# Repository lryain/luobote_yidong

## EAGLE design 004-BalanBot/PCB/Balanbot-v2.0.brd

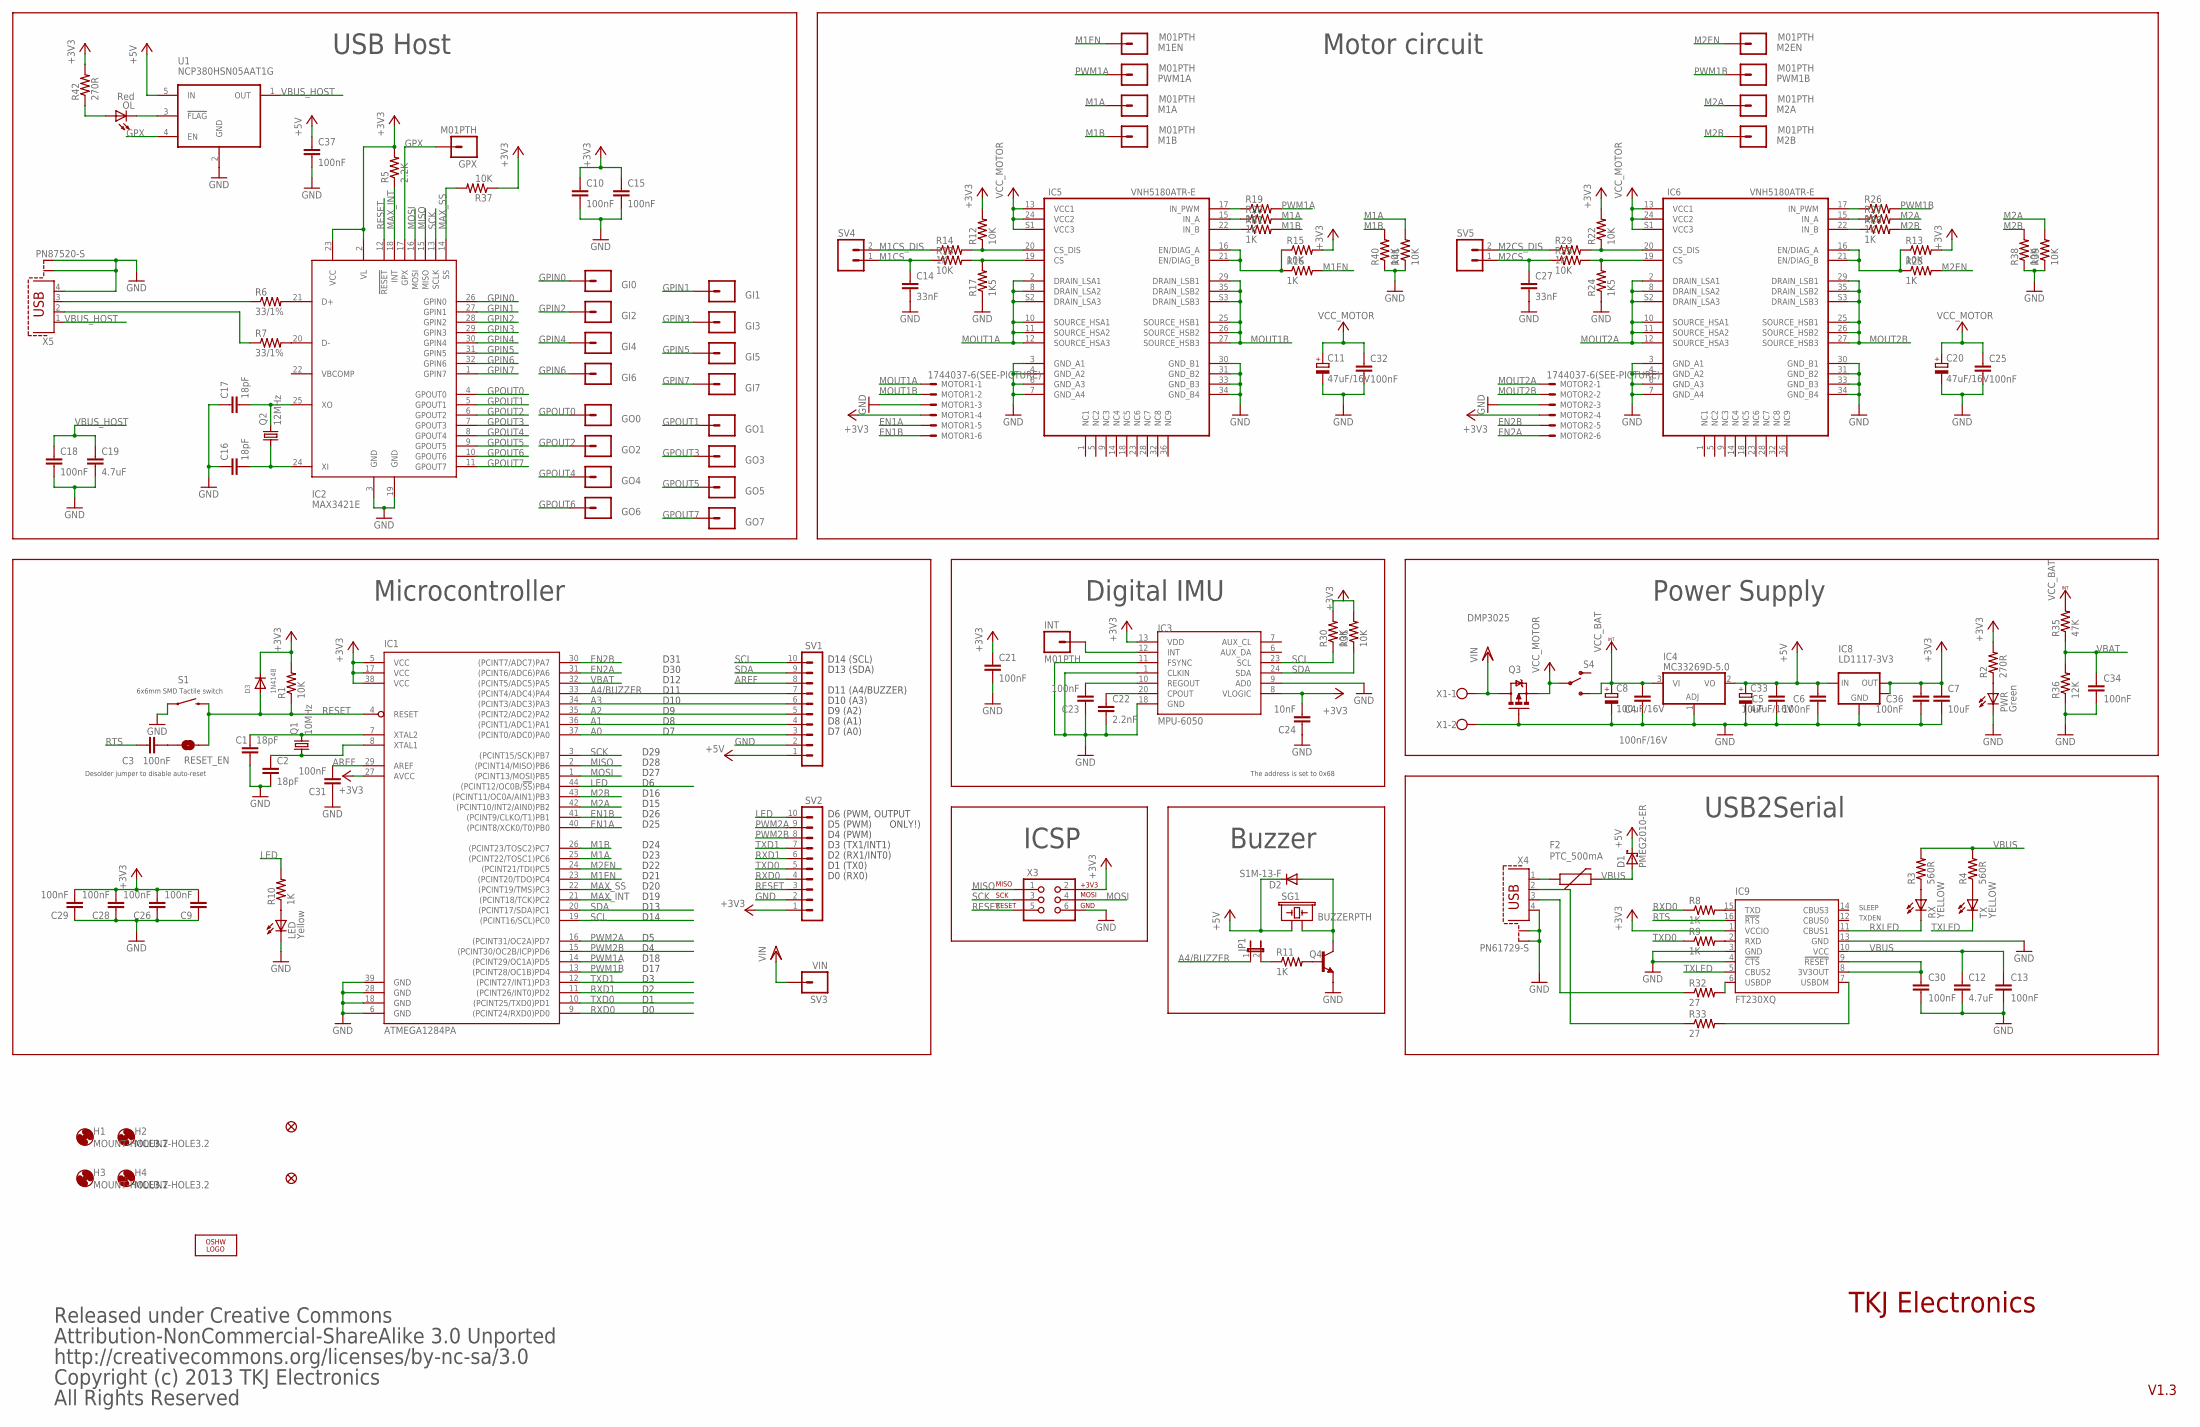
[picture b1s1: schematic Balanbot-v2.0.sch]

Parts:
C1, C2, C16, C17: 18pF; C0603
C3, C6, C9, C10, C13, C15, C18, C21, C23, C25, C26, C28, C29, C30, C31, C32, C34, C36, C37: 100nF; C0603
C4: 100nF/16V; C0603
C5, C7: 10uF; C0805
C8: 100uF/16V; PANASONIC_D
C11, C20, C33: 47uF/16V; PANASONIC_C
C12, C19: 4.7uF; C0805
C14, C27: 33nF; C0603
C22: 2.2nF; C0603
C24: 10nF; C0603
D1: PMEG2010-ER; SOD123
D2: S1M-13-F; DO214AC
D3: 1N4148; SOD-523
F2: PTC_500mA; PTC-1206
GI0, GI1, GI2, GI3, GI4, GI5, GI6, GI7: M01PTH; 1X01
GO0, GO1, GO2, GO3, GO4, GO5, GO6, GO7: M01PTH; 1X01
GPX: M01PTH; 1X01
H1, H2, H3, H4: MOUNT-HOLE3.2; 3,2
IC1: ATMEGA1284PA; TQFP44
IC2: MAX3421E; TQFP32_8MIL
IC3: MPU-6050; TESTING_QFN-24-4MM2
IC4: MC33269D-5.0; DPACK
IC5, IC6: VNH5180ATR-E; POWERSSO-36
IC8: LD1117-3V3; SOT223
IC9: FT230XQ; QFN16
INT: M01PTH; 1X01
JP1: JP1E; JP1
JP2: FIDUCIALUFIDUCIAL; MICRO-FIDUCIAL
JP3: FIDUCIAL1X2; FIDUCIAL-1X2
LED: Yellow; CHIPLED_0805
LOGO2: OSHW_LOGO_FILLX0200-NT; OSHW_FILLX200_NOTEXT
M1A, M1B, M1EN, M2A, M2B, M2EN: M01PTH; 1X01
MOTOR1, MOTOR2: 1744037-6(SEE-PICTURE); 22-23-2061
OL: Red; CHIPLED_0805
PWM1A, PWM1B: M01PTH; 1X01
PWR: Green; CHIPLED_0805
Q1: 10MHz; HC49UP
Q2: 12MHz; HC49UP
Q3: DMP3025; DPAK
Q4: TRANSISTOR_NPNSOT23-3; SOT23-3
R1, R12, R13, R15, R18, R22, R25, R30, R31, R37, R38, R39, R40, R41: 10K; R0603
R2, R42: 270R; R0603
R3, R4: 560R; R0603
R5: 2.2K; R0603
R6, R7: 33/1%; R0603
R8, R9, R10, R11, R14, R16, R19, R20, R21, R23, R26, R27, R28, R29: 1K; R0603
R17, R24: 1K5; R0603
R32, R33: 27; R0603
R35: 47K; R0603
R36: 12K; R0603
RESET_EN: SOLDERJUMPERNC; SJ_2S
RX: YELLOW; CHIPLED_0805
S1: DTSM-62K-S-V-T/R(SN431); TACTILE_SWITCH_TALL
S4: SWITCH-SPDTML; SWITCH-SPDT
SG1: BUZZERPTH; BUZZER-12MM
SV1, SV2: MA10-1
SV3: VIN; 1X01
SV4, SV5: M02PTH; 1X02
TX: YELLOW; CHIPLED_0805
U1: NCP380HSN05AAT1G; SOT23-5
X1: W237-102
X3: AVR_SPI_PRG_62X3_LOCK; 2X3_LOCK
X4: PN61729-S
X5: PN87520-S

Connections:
+3V3: C7.1, C9.2, C10.1, C15.1, C21.1, C24.2, C26.2, C28.2, C29.2, C36.2, D3.K (C), IC1.5 (VCC), IC1.17 (VCC), IC1.27 (AVCC), IC1.38 (VCC), IC2.2 (VL), IC2.23 (VCC), IC3.8 (VLOGIC), IC3.13 (VDD), IC8.2 (OUT), IC8.4 (OUT), IC9.1 (VCCIO), MOTOR1.4, MOTOR2.4, R1.2, R2.2, R5.2, R12.2, R13.2, R15.2, R22.2, R30.2, R31.2, R37.1, R42.2, SV2.1, X3.2
+5V: C5.1, C6.2, C33.+, C37.1, D1.C, D2.C, IC4.2 (VO), IC8.3 (IN), SG1.+ (1), SV1.1, U1.5 (IN)
A0: IC1.37 ((PCINT0/ADC0)PA0), SV1.3
A1: IC1.36 ((PCINT1/ADC1)PA1), SV1.4
A2: IC1.35 ((PCINT2/ADC2)PA2), SV1.5
A3: IC1.34 ((PCINT3/ADC3)PA3), SV1.6
A4/BUZZER: IC1.33 ((PCINT4/ADC4)PA4), JP1.1, SV1.7
AREF: C31.2, IC1.29 (AREF), SV1.8
EN1A: IC1.40 ((PCINT8/XCK0/T0)PB0), MOTOR1.5
EN1B: IC1.41 ((PCINT9/CLKO/T1)PB1), MOTOR1.6
EN2A: IC1.31 ((PCINT6/ADC6)PA6), MOTOR2.6
EN2B: IC1.30 ((PCINT7/ADC7)PA7), MOTOR2.5
GND: C1.1, C2.2, C4.1, C5.2, C6.1, C7.2, C8.-, C9.1, C10.2, C11.-, C12.2, C13.1, C14.2, C15.2, C16.1, C17.1, C18.2, C19.2, C20.-, C21.2, C22.2, C23.1, C24.1, C25.2, C26.1, C27.2, C28.1, C29.1, C30.1, C31.1, C32.2, C33.-, C34.1, C36.1, C37.2, IC1.6 (GND), IC1.18 (GND), IC1.28 (GND), IC1.39 (GND), IC2.3 (GND), IC2.19 (GND), IC3.1 (CLKIN), IC3.9 (AD0), IC3.11 (FSYNC), IC3.18 (GND), IC4.1 (ADJ), IC5.3 (GND_A1), IC5.4 (GND_A2), IC5.6 (GND_A3), IC5.7 (GND_A4), IC5.30 (GND_B1), IC5.31 (GND_B2), IC5.33 (GND_B3), IC5.34 (GND_B4), IC6.3 (GND_A1), IC6.4 (GND_A2), IC6.6 (GND_A3), IC6.7 (GND_A4), IC6.30 (GND_B1), IC6.31 (GND_B2), IC6.33 (GND_B3), IC6.34 (GND_B4), IC8.1 (GND), IC9.3 (GND), IC9.4 (!CTS), IC9.13 (GND), LED.C, MOTOR1.3, MOTOR2.3, PWR.C, Q3.1 (G), Q4.2 (E), R17.1, R24.1, R36.1, R38.1, R39.1, R40.1, R41.1, S1.A2 (1), SV1.2, SV2.2, U1.2 (GND), X1.2, X3.6, X4.4, X4.S1, X4.S2, X5.4, X5.S1, X5.S2
GPIN0: GI0.1, IC2.26 (GPIN0)
GPIN1: GI1.1, IC2.27 (GPIN1)
GPIN2: GI2.1, IC2.28 (GPIN2)
GPIN3: GI3.1, IC2.29 (GPIN3)
GPIN4: GI4.1, IC2.30 (GPIN4)
GPIN5: GI5.1, IC2.31 (GPIN5)
GPIN6: GI6.1, IC2.32 (GPIN6)
GPIN7: GI7.1, IC2.1 (GPIN7)
GPOUT0: GO0.1, IC2.4 (GPOUT0)
GPOUT1: GO1.1, IC2.5 (GPOUT1)
GPOUT2: GO2.1, IC2.6 (GPOUT2)
GPOUT3: GO3.1, IC2.7 (GPOUT3)
GPOUT4: GO4.1, IC2.8 (GPOUT4)
GPOUT5: GO5.1, IC2.9 (GPOUT5)
GPOUT6: GO6.1, IC2.10 (GPOUT6)
GPOUT7: GO7.1, IC2.11 (GPOUT7)
GPX: GPX.1, IC2.17 (GPX), U1.4 (EN)
LED: IC1.44 ((PCINT12/OC0B/!SS!)PB4), R10.2, SV2.10
M1A: IC1.25 ((PCINT22/TOSC1)PC6), M1A.1, R20.2, R41.2
M1B: IC1.26 ((PCINT23/TOSC2)PC7), M1B.1, R21.2, R40.2
M1CS: C14.1, R18.1, SV4.1
M1CS_DIS: R14.1, SV4.2
M1EN: IC1.23 ((PCINT20/TDO)PC4), M1EN.1, R16.2
M2A: IC1.42 ((PCINT10/INT2/AIN0)PB2), M2A.1, R27.2, R39.2
M2B: IC1.43 ((PCINT11/OC0A/AIN1)PB3), M2B.1, R28.2, R38.2
M2CS: C27.1, R25.1, SV5.1
M2CS_DIS: R29.1, SV5.2
M2EN: IC1.24 ((PCINT21/TDI)PC5), M2EN.1, R23.2
MAX_INT: IC1.21 ((PCINT18/TCK)PC2), IC2.18 (INT), R5.1
MAX_SS: IC1.22 ((PCINT19/TMS)PC3), IC2.14 (SS), R37.2
MISO: IC1.2 ((PCINT14/MISO)PB6), IC2.15 (MISO), X3.1
MOSI: IC1.1 ((PCINT13/MOSI)PB5), IC2.16 (MOSI), X3.4
MOUT1A: IC5.2 (DRAIN_LSA1), IC5.8 (DRAIN_LSA2), IC5.10 (SOURCE_HSA1), IC5.11 (SOURCE_HSA2), IC5.12 (SOURCE_HSA3), IC5.S2 (DRAIN_LSA3), MOTOR1.1
MOUT1B: IC5.25 (SOURCE_HSB1), IC5.26 (SOURCE_HSB2), IC5.27 (SOURCE_HSB3), IC5.29 (DRAIN_LSB1), IC5.35 (DRAIN_LSB2), IC5.S3 (DRAIN_LSB3), MOTOR1.2
MOUT2A: IC6.2 (DRAIN_LSA1), IC6.8 (DRAIN_LSA2), IC6.10 (SOURCE_HSA1), IC6.11 (SOURCE_HSA2), IC6.12 (SOURCE_HSA3), IC6.S2 (DRAIN_LSA3), MOTOR2.1
MOUT2B: IC6.25 (SOURCE_HSB1), IC6.26 (SOURCE_HSB2), IC6.27 (SOURCE_HSB3), IC6.29 (DRAIN_LSB1), IC6.35 (DRAIN_LSB2), IC6.S3 (DRAIN_LSB3), MOTOR2.2
unnamed: C3.2, RESET_EN.1
unnamed: C2.1, IC1.8 (XTAL1), Q1.1
unnamed: C1.2, IC1.7 (XTAL2), Q1.2
unnamed: D2.A, Q4.3 (C), SG1.- (2)
unnamed: JP1.2, R11.1
unnamed: R33.1, X4.2
unnamed: LED.A, R10.1
unnamed: OL.A, R42.1
unnamed: PWR.A, R2.1
unnamed: R32.1, X4.3
unnamed: IC9.7 (USBDM), R33.2
unnamed: OL.C, U1.3 (!FLAG)
unnamed: IC2.20 (D-), R7.2
unnamed: IC2.21 (D+), R6.2
unnamed: R6.1, X5.3
unnamed: R7.1, X5.2
unnamed: C17.2, IC2.25 (XO), Q2.2
unnamed: C16.2, IC2.24 (XI), Q2.1
unnamed: IC3.12 (INT), INT.1
unnamed: C22.1, IC3.20 (CPOUT)
unnamed: C23.2, IC3.10 (REGOUT)
unnamed: IC6.16 (EN/DIAG_A), IC6.21 (EN/DIAG_B), R13.1, R23.1
unnamed: IC6.19 (CS), R24.2, R25.2
unnamed: IC5.16 (EN/DIAG_A), IC5.21 (EN/DIAG_B), R15.1, R16.1
unnamed: Q4.1 (B), R11.2
unnamed: IC5.19 (CS), R17.2, R18.2
unnamed: IC5.20 (CS_DIS), R12.1, R14.2
unnamed: IC5.22 (IN_B), R21.1
unnamed: IC5.15 (IN_A), R20.1
unnamed: IC5.17 (IN_PWM), R19.1
unnamed: IC6.22 (IN_B), R28.1
unnamed: IC6.15 (IN_A), R27.1
unnamed: IC6.17 (IN_PWM), R26.1
unnamed: IC6.20 (CS_DIS), R22.1, R29.2
unnamed: F2.1, X4.1
unnamed: IC9.15 (TXD), R8.2
unnamed: IC9.2 (RXD), R9.2
unnamed: IC9.6 (USBDP), R32.2
unnamed: C30.2, IC9.8 (3V3OUT), IC9.9 (!RESET)
unnamed: R3.1, RX.A
unnamed: R4.1, TX.A
PWM1A: IC1.14 ((PCINT29/OC1A)PD5), PWM1A.1, R19.2
PWM1B: IC1.13 ((PCINT28/OC1B)PD4), PWM1B.1, R26.2
PWM2A: IC1.16 ((PCINT31/OC2A)PD7), SV2.9
PWM2B: IC1.15 ((PCINT30/OC2B/ICP)PD6), SV2.8
RESET: D3.A, IC1.4 (RESET), IC2.12 (!RESET), R1.1, RESET_EN.2, S1.B2 (2), SV2.3, X3.5
RTS: C3.1, IC9.16 (!RTS)
RXD0: IC1.9 ((PCINT24/RXD0)PD0), R8.1, SV2.4
RXD1: IC1.11 ((PCINT26/INT0)PD2), SV2.6
RXLED: IC9.11 (CBUS1), RX.C
SCK: IC1.3 ((PCINT15/SCK)PB7), IC2.13 (SCLK), X3.3
SCL: IC1.19 ((PCINT16/SCL)PC0), IC3.23 (SCL), R30.1, SV1.10
SDA: IC1.20 ((PCINT17/SDA)PC1), IC3.24 (SDA), R31.1, SV1.9
TXD0: IC1.10 ((PCINT25/TXD0)PD1), R9.1, SV2.5
TXD1: IC1.12 ((PCINT27/INT1)PD3), SV2.7
TXLED: IC9.5 (CBUS2), TX.C
VBAT: C34.2, IC1.32 ((PCINT5/ADC5)PA5), R35.1, R36.2
VBUS: C12.1, C13.2, D1.A, F2.2, IC9.10 (VCC), R3.2, R4.2
VBUS_HOST: C18.1, C19.1, U1.1 (OUT), X5.1
VCC: C11.+, C20.+, C25.1, C32.1, IC5.13 (VCC1), IC5.24 (VCC2), IC5.S1 (VCC3), IC6.13 (VCC1), IC6.24 (VCC2), IC6.S1 (VCC3), Q3.3 (S), S4.2
VCC_INT: C4.2, C8.+, IC4.3 (VI), R35.2, S4.1 (S)
VDD: Q3.4 (D), SV3.1, X1.1

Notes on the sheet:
Desolder jumper to disable auto-reset
ICSP
Power Supply
D10
D11
D12
D30
D31
D14
D13
D19
D20
D21
D22
D23
D24
D25
D26
D15
D17
D18
D16
D27
D28
D29
D0 (RX0)
D1 (TX0)
D2 (RX1/INT0)
D13 (SDA)
D14 (SCL)
D5 (PWM)
D6 (PWM, OUTPUT
D4 (PWM)
D3 (TX1/INT1)
D10 (A3)
D9 (A2)
D8 (A1)
D7 (A0)
USB2Serial
Digital IMU

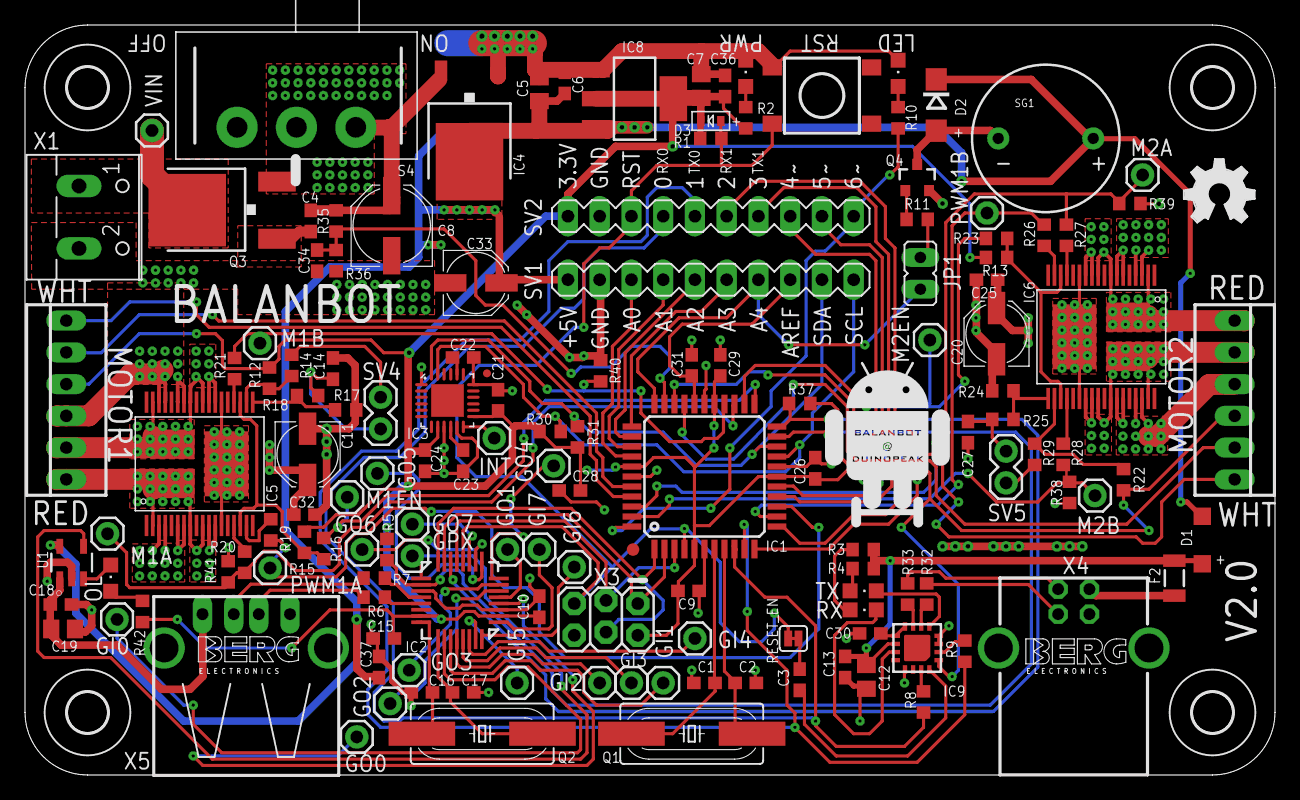
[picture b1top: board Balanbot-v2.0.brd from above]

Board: 2 copper layers, 100.0 x 60.0 mm, 150 parts (1 on the bottom side), 111 nets.

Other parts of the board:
U$2: DUINOPEAK-ANDROID-LOGO-0.65
U$3: DUINOPEAK-ANDROID-LOGO-3.5

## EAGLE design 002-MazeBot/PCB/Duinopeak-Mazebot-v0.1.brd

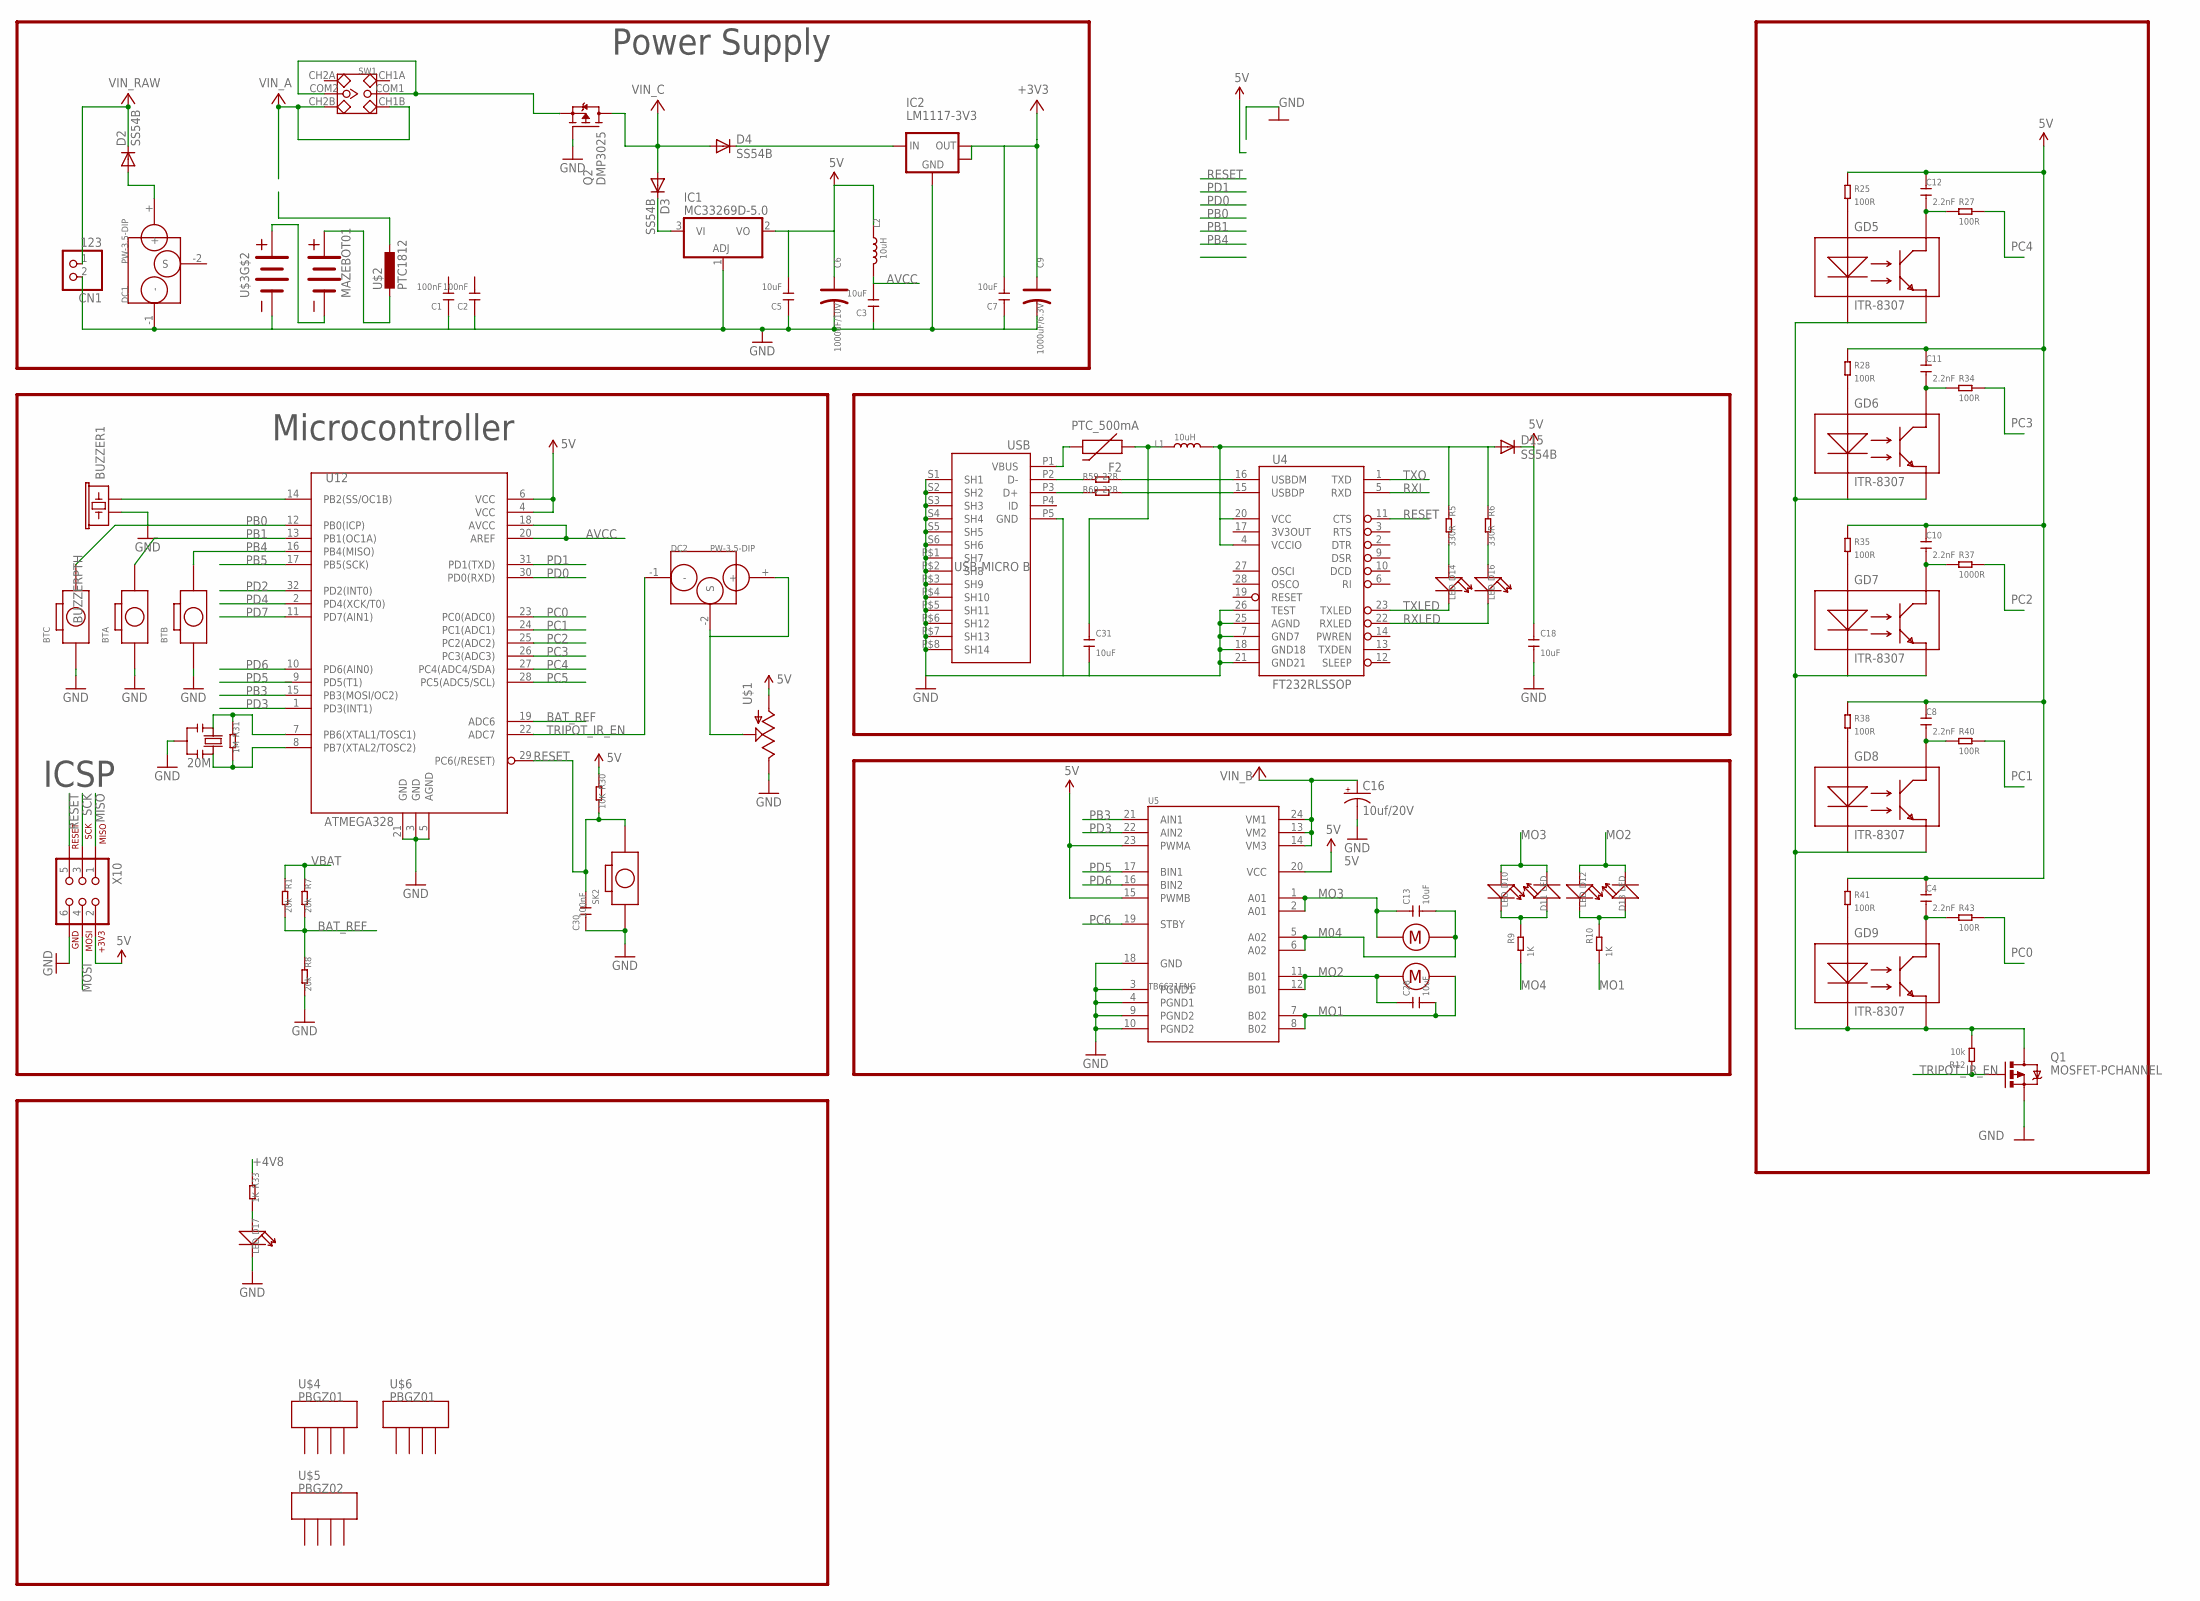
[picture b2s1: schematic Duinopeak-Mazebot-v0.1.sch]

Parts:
BTA: BOTTON-2P-90; 2P-7.62X3.56-90D
BTB: BOTTON-2P-90; 2P-7.62X3.56-90D
BTC: BOTTON-2P-90; 2P-7.62X3.56-90D
BUZZER1: BUZZERPTH; BUZZER-12MM
C1, C2, C30: 100nF; C0603
C3, C5, C7, C13, C28, C31: 10uF; C0805
C4, C8, C10, C11, C12: 2.2nF; C0603
C6: 1000uF/10V; ELECTRO-8.2MM
C9: 1000uF/6.3V; ELECTRO-8.2MM
C16: 10uf/20V; EIA3216
C18: 10uF; C0603
CN1: 123; JST-PH-2-SMT-RA
D2, D3, D4, D15: SS54B; SMB
D10, D11, D12, D13, D14, D16, D17: LED; LED-0603
DC1, DC2: PW-3.5-DIP
F2: PTC_500mA; PTC-1206
GD5, GD6, GD7, GD8, GD9: ITR-8307
IC1: MC33269D-5.0; DPACK
IC2: LM1117-3V3; SOT223
L1, L2: 10uH; L0805
Q1: MOSFET-PCHANNEL; SOT23
Q2: DMP3025; TO252
R1, R7, R8: 20k; R0603
R5, R6: 330R; R0603
R9, R10, R33: 1K; R0603
R12: 10k; R0603
R25, R27, R28, R34, R35, R38, R40, R41, R43: 100R; R0603
R30: 10K; R0603
R31: 1M; R0603
R37: 1000R; R0603
R59, R60: 22R; R0603
SK2: BOTTON-2P-90; 2P-7.62X3.56-90D
SW1: SWITCH-2CH-6P'90D'; 6P-2CH-2.54-9.0X3.6-90D
U4: FT232RLSSOP; SSOP28DB
U5: TB6621FNG; SSOP24
U12: ATMEGA328; TQFP32-08
U$1: POTTRIM; TRIM_POT
U$2: PTC1812; PTC-L1812
U$3: MAZEBOT01; MAZEBOT-P1
U$4, U$6: PBGZ01; PBGZ-22X33MM
U$5: PBGZ02; PBGZ-20X55MM
USB: USB-MICRO B; CON2_USB_MICRO_B_AT
X10: AVR_SPI_PRG_62X3_LOCK; 2X3_LOCK
Y1: 20M; RESONATOR

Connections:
5V: C4.2, C5.1, C6.1 (+), C8.2, C10.2, C11.2, C12.2, C18.2, D15.C, IC1.2 (VO), L2.1, R25.1, R28.1, R30.1, R35.1, R38.1, R41.1, U5.15 (PWMB), U5.20 (VCC), U5.23 (PWMA), U12.4 (VCC), U12.6 (VCC), U$1.3 (A), X10.2
+3V3: C7.1, C9.1 (+), IC2.2 (OUT), IC2.4 (OUT)
+4V8: R33.1
AVCC: C3.1, L2.2, U12.18 (AVCC), U12.20 (AREF)
BAT_REF: R1.2, R7.2, R8.1, U12.19 (ADC6)
DCA: CN1.1 (2), D2.C
DCB: SW1.CH1B, SW1.CH2B
GND: BTA.P$1 (1), BTB.P$1 (1), BTC.P$1 (1), BUZZER1.+ (1), C1.2, C2.2, C3.2, C5.2, C6.2 (-), C7.2, C9.2 (-), C16.C (-), C18.1, C30.2, C31.1, CN1.2 (1), D17.-, DC1.-1 (-), IC1.1 (ADJ), IC2.1 (GND), Q1.2 (S), Q2.1 (G), R8.2, SK2.P$1 (1), U4.7 (GND7), U4.18 (GND18), U4.21 (GND21), U4.25 (AGND), U4.26 (TEST), U5.3 (PGND1), U5.4 (PGND1), U5.9 (PGND2), U5.10 (PGND2), U5.18 (GND), U12.3 (GND), U12.5 (AGND), U12.21 (GND), U$1.2 (E), U$3.D1, USB.P5 (GND), USB.P$1 (SH7), USB.P$2 (SH8), USB.P$3 (SH9), USB.P$4 (SH10), USB.P$5 (SH11), USB.P$6 (SH12), USB.P$7 (SH13), USB.P$8 (SH14), USB.S1 (SH1), USB.S2 (SH2), USB.S3 (SH3), USB.S4 (SH4), USB.S5 (SH5), USB.S6 (SH6), X10.6, Y1.2
M04: C13.1, U5.5 (A02), U5.6 (A02), U$3.M2
MISO: X10.1
MO1: C28.1, R10.2, U5.7 (B02), U5.8 (B02), U$3.M4
MO2: C28.2, D12.+, D13.-, U5.11 (B01), U5.12 (B01), U$3.M3
MO3: C13.2, D10.+, D11.-, U5.1 (A01), U5.2 (A01), U$3.M1
MO4: R9.2
MOSI: X10.4
unnamed: R31.1, U12.7 (PB6(XTAL1/TOSC1)), Y1.1
unnamed: R31.2, U12.8 (PB7(XTAL2/TOSC2)), Y1.3
unnamed: D14.+, R5.2
unnamed: D16.+, R6.2
unnamed: D10.-, D11.+, R9.1
unnamed: D17.+, R33.2
unnamed: C31.2, F2.1, L1.1
unnamed: GD5.2, GD5.4, GD6.2, GD6.4, GD7.2, GD7.4, GD8.2, GD8.4, GD9.2, GD9.4, Q1.3 (D), R12.2
unnamed: DC2.+, DC2.-2 (S), U$1.1 (S)
unnamed: BUZZER1.- (2), U12.14 (PB2(SS/OC1B))
unnamed: D12.-, D13.+, R10.1
unnamed: C12.1, GD5.3, R27.2
unnamed: U$3.D2, U$3.D3
unnamed: U$2.1, U$3.D4
unnamed: D4.C, IC2.3 (IN)
unnamed: D3.C, IC1.3 (VI)
unnamed: F2.2, USB.P1 (VBUS)
unnamed: R59.1, USB.P2 (D-)
unnamed: GD5.1, R25.2
unnamed: GD6.1, R28.2
unnamed: C10.1, GD7.3, R37.2
unnamed: GD7.1, R35.2
unnamed: C8.1, GD8.3, R40.2
unnamed: D15.A, L1.2, R5.1, R6.1, U4.4 (VCCIO), U4.20 (VCC)
unnamed: GD8.1, R38.2
unnamed: C4.1, GD9.3, R43.2
unnamed: GD9.1, R41.2
unnamed: R60.1, USB.P3 (D+)
unnamed: D2.A, DC1.+
unnamed: C11.1, GD6.3, R34.2
PB0: BTC.P$2 (2), U12.12 (PB0(ICP))
PB1: BTA.P$2 (2), U12.13 (PB1(OC1A))
PB3: U5.21 (AIN1), U12.15 (PB3(MOSI/OC2))
PB4: BTB.P$2 (2), U12.16 (PB4(MISO))
PB5: U12.17 (PB5(SCK))
PC0: R43.1, U12.23 (PC0(ADC0))
PC1: R40.1, U12.24 (PC1(ADC1))
PC2: R37.1, U12.25 (PC2(ADC2))
PC3: R34.1, U12.26 (PC3(ADC3))
PC4: R27.1, U12.27 (PC4(ADC4/SDA))
PC5: U12.28 (PC5(ADC5/SCL))
PC6: U5.19 (STBY)
PD0: U12.30 (PD0(RXD))
PD1: U12.31 (PD1(TXD))
PD2: U12.32 (PD2(INT0))
PD3: U5.22 (AIN2), U12.1 (PD3(INT1))
PD4: U12.2 (PD4(XCK/T0))
PD5: U5.17 (BIN1)
PD6: U5.16 (BIN2), U12.10 (PD6(AIN0))
PD7: U12.11 (PD7(AIN1))
RESET: C30.1, R30.2, SK2.P$2 (2), U4.11 (CTS), U12.29 (PC6(/RESET)), X10.5
RXI: U4.5 (RXD)
RXLED: D16.-, U4.22 (RXLED)
SCK: X10.3
TRIPOT_IR_EN: DC2.-1 (-), Q1.1 (G), R12.1, U12.22 (ADC7)
TXLED: D14.-, U4.23 (TXLED)
TXO: U4.1 (TXD)
USB_D+: R60.2, U4.15 (USBDP)
USB_D-: R59.2, U4.16 (USBDM)
VBAT: R1.1, R7.1
VIN_B: Q2.2 (S), SW1.COM1, SW1.COM2
VIN_C: C16.A (+), D3.A, D4.A, Q2.3 (D), U5.13 (VM2), U5.14 (VM3), U5.24 (VM1)

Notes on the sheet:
Power Supply
Microcontroller
ICSP

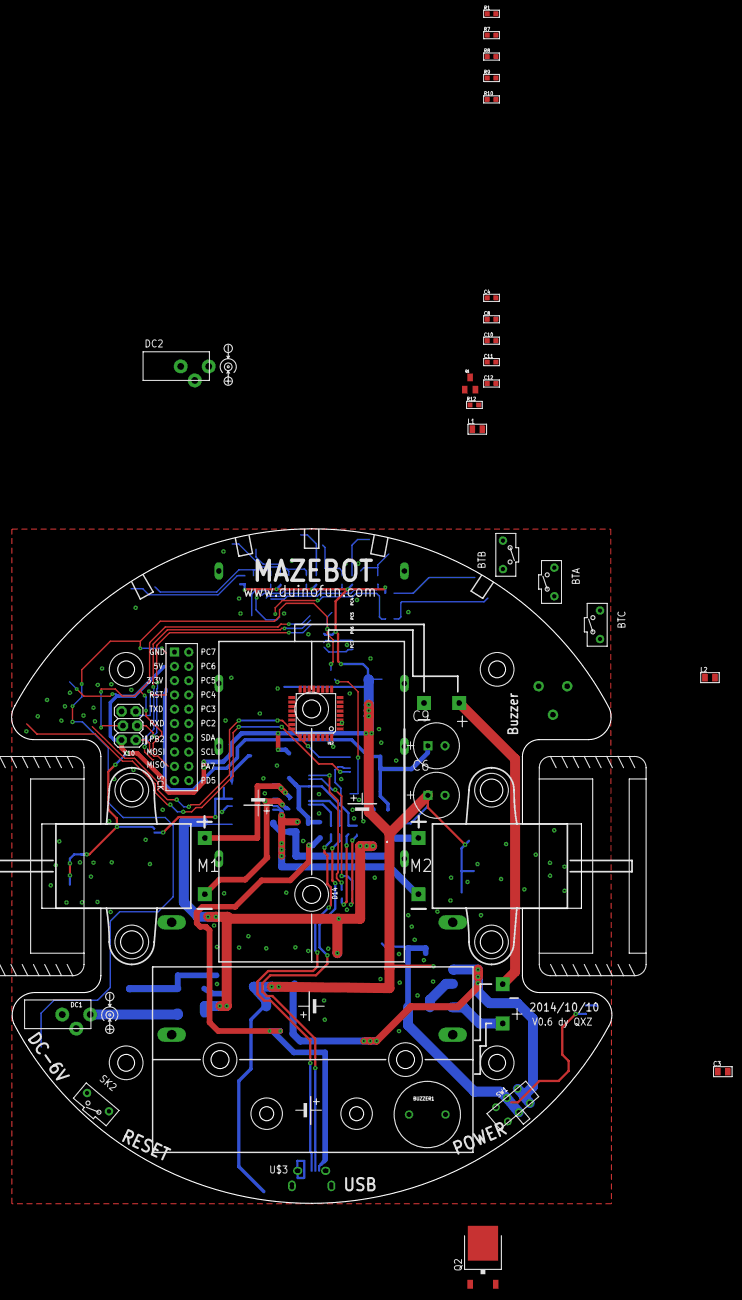
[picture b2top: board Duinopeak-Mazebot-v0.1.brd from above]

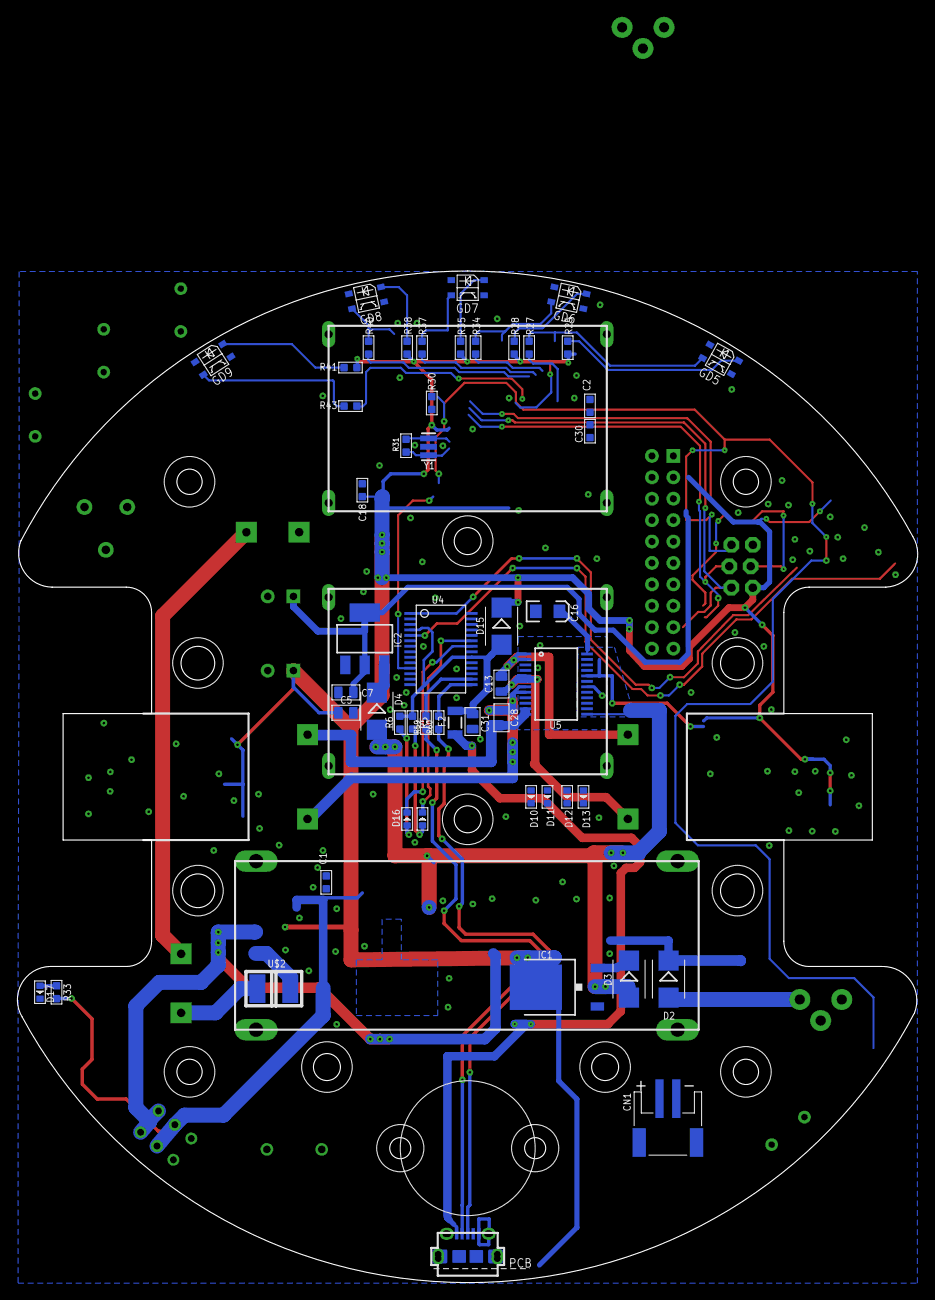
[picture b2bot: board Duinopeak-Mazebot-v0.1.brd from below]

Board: 2 copper layers, 106.8 x 120.0 mm, 85 parts (55 on the bottom side), 61 nets.

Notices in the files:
004-BalanBot/PCB/Balanbot-v2.0.sch:
Released under Creative Commons
http://creativecommons.org/licenses/by-nc-sa/3.0
Copyright (c) 2013 TKJ Electronics
All Rights Reserved
parts and their libraries:
SparkFun: Licensing: CC v3.0 Share-Alike You are welcome to use this library for commercial purposes.
